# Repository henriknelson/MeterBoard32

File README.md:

# MeterBoard32
KiCad hardware project to integrate Texas Instruments TSS721-ADR M-Bus transceiver with Espressifs ESP32-WROOM module on a single PCB.

3D View:

Schematic:

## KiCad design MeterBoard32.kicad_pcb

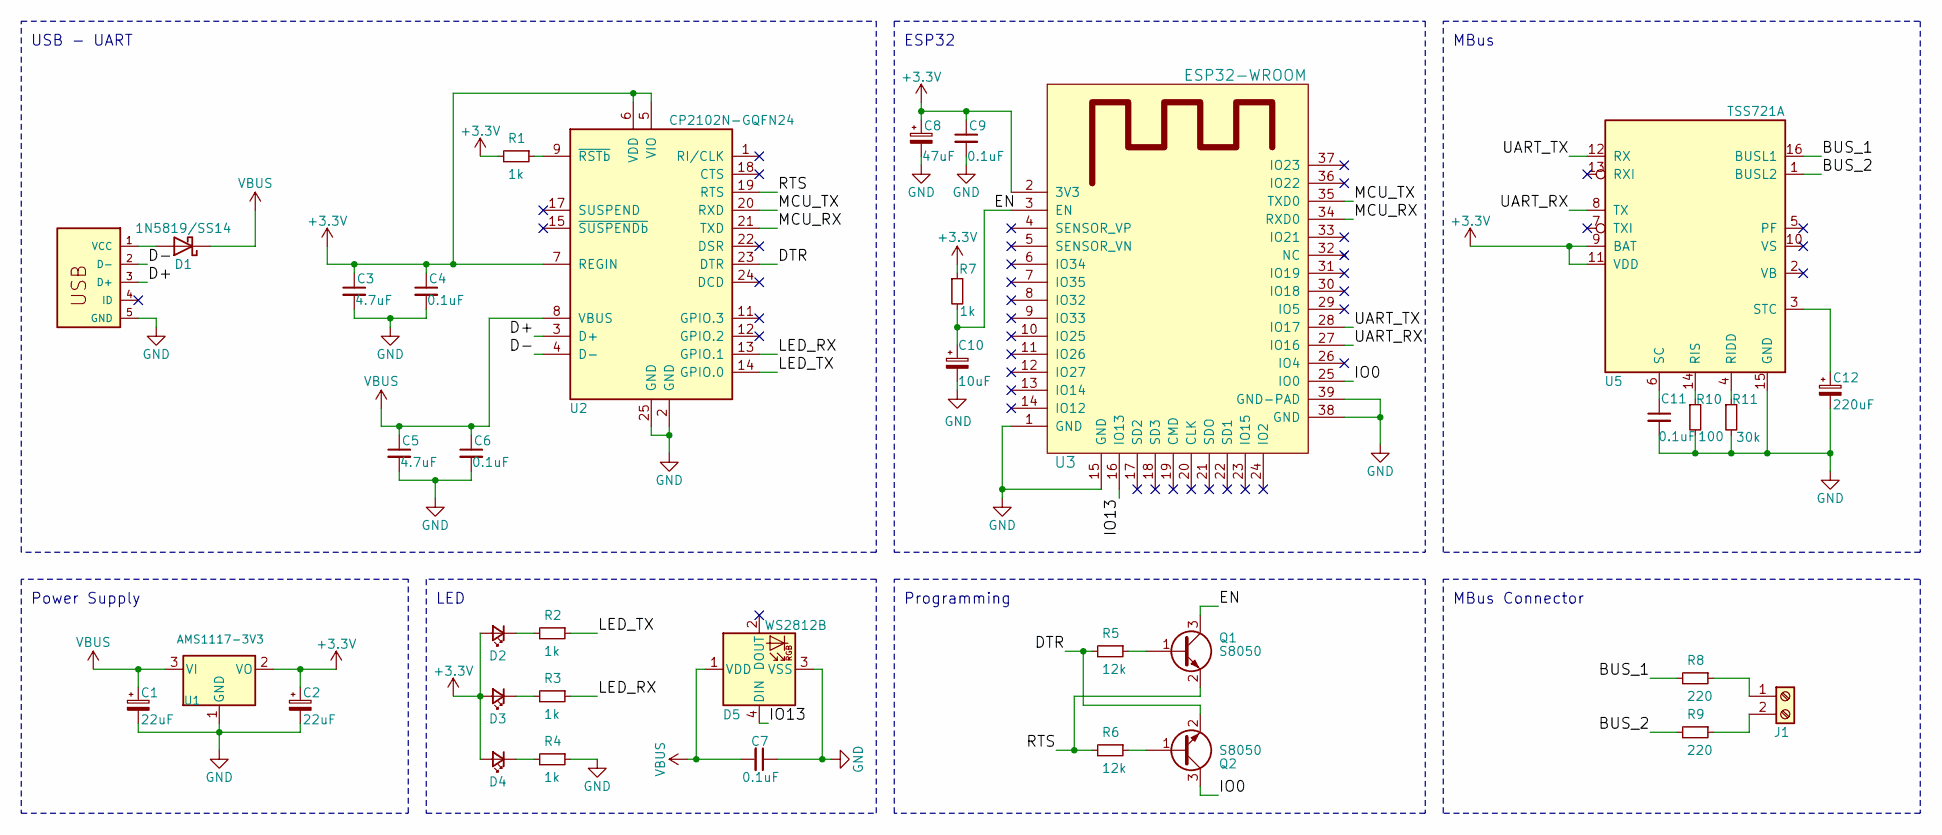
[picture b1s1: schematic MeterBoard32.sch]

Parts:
C1, C2: 22uF; C_1206_3216Metric_Pad1.33x1.80mm_HandSolder
C3, C5: 4.7uF; C_1206_3216Metric_Pad1.33x1.80mm_HandSolder
C4, C6, C7, C9, C11: 0.1uF; C_1206_3216Metric_Pad1.33x1.80mm_HandSolder
C8: 47uF; C_1206_3216Metric_Pad1.33x1.80mm_HandSolder
C10: 10uF; C_1206_3216Metric_Pad1.33x1.80mm_HandSolder
C12: 220uF; CP_EIA-7343-31_Kemet-D_Pad2.25x2.55mm_HandSolder
D1: 1N5819/SS14; D_SOD-123F
D2, D3, D4: LED_Small; LED_1206_3216Metric_Pad1.42x1.75mm_HandSolder
D5: WS2812B; LED_WS2812B_PLCC4_5.0x5.0mm_P3.2mm
J1: Screw_Terminal_01x02; TERMINAL_BLOCK_WJ126V_5_0_2P
M1: MICRO_USB_18_TH
Q1, Q2: S8050; SOT-23_Handsoldering
R1, R2, R3, R4, R7: 1k; R_1206_3216Metric_Pad1.30x1.75mm_HandSolder
R5, R6: 12k; R_1206_3216Metric_Pad1.30x1.75mm_HandSolder
R8, R9: 220; R_1206_3216Metric_Pad1.30x1.75mm_HandSolder
R10: 100; R_1206_3216Metric_Pad1.30x1.75mm_HandSolder
R11: 30k; R_1206_3216Metric_Pad1.30x1.75mm_HandSolder
U1: AMS1117-3V3; SOT-223
U2: CP2102N-GQFN24; QFN-24-1EP_4x4mm_P0.5mm_EP2.6x2.6mm
U3: ESP32-WROOM
U5: TSS721A; SOIC-16_3.9x9.9mm_P1.27mm

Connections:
+3V3: C2.1, C3.1, C4.1, C8.1, C9.1, D2.2 (A), D3.2 (A), D4.2 (A), R1.2, R7.1, U1.2 (VO), U2.5 (VIO), U2.6 (VDD), U2.7 (REGIN), U3.2 (3V3), U5.9 (BAT), U5.11 (VDD)
/BUS_1: R8.2, U5.16 (BUSL1)
/BUS_2: R9.2, U5.1 (BUSL2)
/D+: M1.3 (D+), U2.3 (D+)
/D-: M1.2 (D-), U2.4 (D-)
/DTR: Q2.2 (E), R5.2, U2.23 (DTR)
/EN: C10.1, Q1.3 (C), R7.2, U3.3 (EN)
/IO0: Q2.3 (C), U3.25 (IO0)
/IO13: D5.4 (DIN), U3.16 (IO13)
/LED_RX: R3.1, U2.13 (GPIO.1)
/LED_TX: R2.1, U2.14 (GPIO.0)
/MCU_RX: U2.21 (TXD), U3.34 (RXD0)
/MCU_TX: U2.20 (RXD), U3.35 (TXD0)
/RTS: Q1.2 (E), R6.2, U2.19 (RTS)
/UART_RX: U3.27 (IO16), U5.8 (TX)
/UART_TX: U3.28 (IO17), U5.12 (RX)
GND: C1.2, C2.2, C3.2, C4.2, C5.2, C6.2, C7.1, C8.2, C9.2, C10.2, C11.2, C12.2, D5.3 (VSS), M1.5 (GND), R4.1, R10.2, R11.2, U1.1 (GND), U2.2 (GND), U2.25 (GND), U3.1 (GND), U3.15 (GND), U3.38 (GND), U3.39 (GND-PAD), U5.15 (GND)
unnamed: C11.1, U5.6 (SC)
unnamed: C12.1, U5.3 (STC)
unnamed: D1.2 (A), M1.1 (VCC)
unnamed: D2.1 (K), R2.2
unnamed: D3.1 (K), R3.2
unnamed: D4.1 (K), R4.2
unnamed: J1.1, R8.1
unnamed: J1.2, R9.1
unnamed: Q1.1 (B), R5.1
unnamed: Q2.1 (B), R6.1
unnamed: R1.1, U2.9 (~RSTb)
unnamed: R10.1, U5.14 (RIS)
unnamed: R11.1, U5.4 (RIDD)
VBUS: C1.1, C5.1, C6.1, C7.2, D1.1 (K), D5.1 (VDD), U1.3 (VI), U2.8 (VBUS)

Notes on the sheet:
USB - UART
Power Supply
LED
ESP32
Programming
MBus
MBus Connector

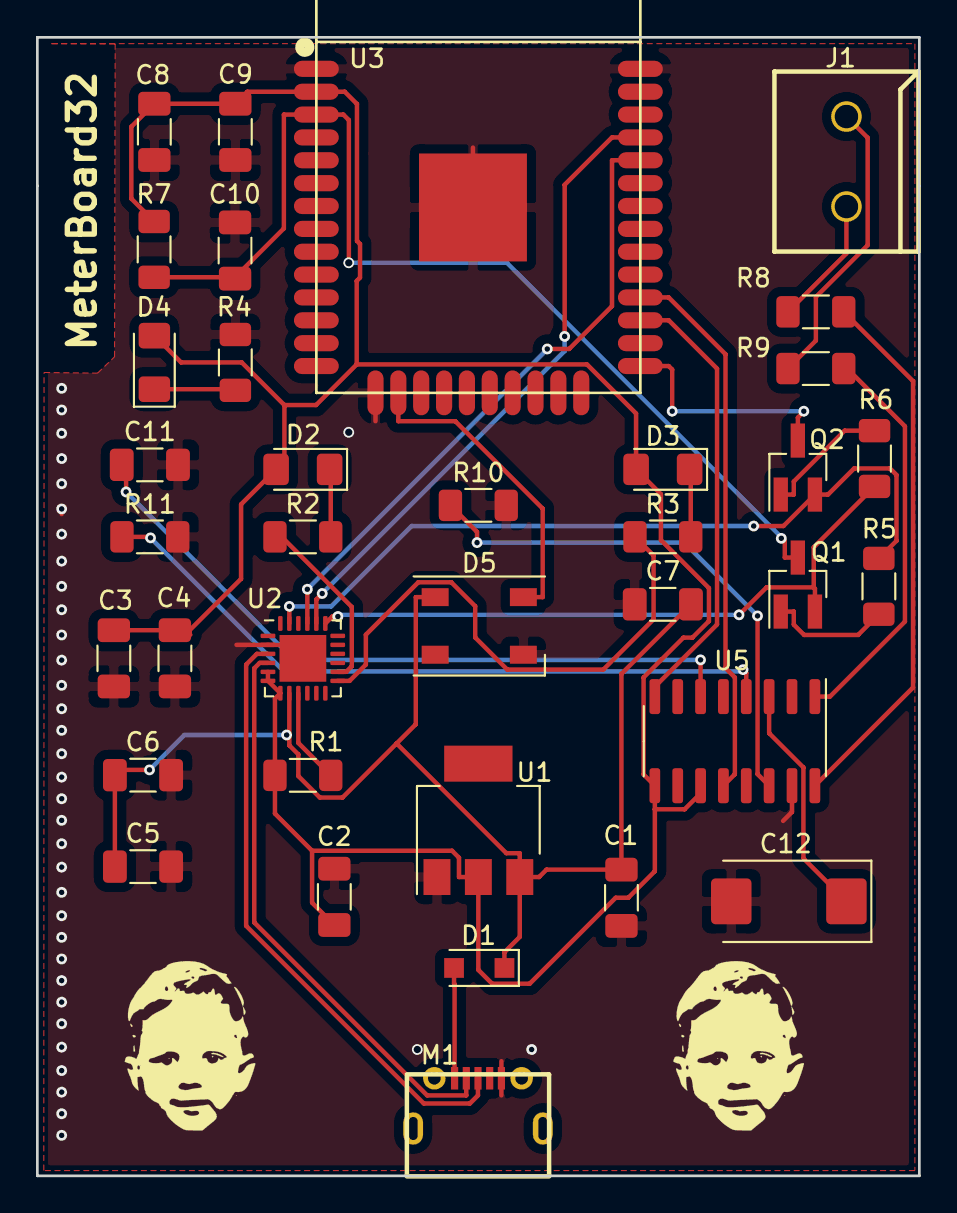
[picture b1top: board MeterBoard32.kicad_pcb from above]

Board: 2 copper layers, 49.0 x 63.3 mm, 38 parts (0 on the bottom side), 31 nets.

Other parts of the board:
G1, G1#2: LOGO; Harry_3

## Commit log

2018-03-16 Added project files
2018-03-17 Added schematics for TSS721A
2018-03-22 cleanup..
2018-03-22 Added README file
2018-03-22 Added KiCad project files
2018-03-22 Changed name from MbusBoard32 to MeterBoard32
2018-03-22 Added Gerber files
2018-03-22 Added Front/Back PCB / 3D images
2018-03-22 Added schematic PDF
2018-03-22 Added additional KiCad files
2018-03-22 Added datasheets
2018-03-22 Cropped 3D image
2018-03-22 Added schematic PNG file
2018-03-22 Updated README with PCB 3D and schematic images
2018-03-22 Added cache/rescue library files
2021-03-30 Updated README
    Some small clarifications
2021-04-01 Small cosmetic fix
2021-04-26 Converted old KiCad 4 project file to KiCad 5
2021-04-26 Small fix
2021-04-26 Small fixes again..
2021-04-26 Fixed 3D models
2021-04-27 Finished the conversion of MeterBoard32 from KiCad 4 to KiCad 5

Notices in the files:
MeterBoard32.kicad_pcb:
© Henrik Nelson
